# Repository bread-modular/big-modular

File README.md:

# Big Modular

A collection of Eurorack modules built with shared KiCad tooling.

## Modules

| Module | Description | Release |
| --- | --- | --- |
| [`usb-power`](modules/usb-power/) | USB-C PD input → protected 9V, dual TPS54302 bucks, TPS65131 raw ±13.5V, TPS7A4700/TPS7A3301 quiet ±12V, +5V | LDO-R1 source; recovered exports STALE |

Each module is self-contained under `modules/<name>/`:

```text
modules/usb-power/
  hardware/     KiCad project (usb-power.kicad_{pro,sch,pcb}, panel, local libs)
  docs/         design, fabrication and evidence notes
  tools/        module generators/checkers
  tests/        module regression tests
  jlcpcb/       recovered Gerber/BOM/CPL snapshot (STALE until re-export)
```

## Common tooling

`opt/` holds shared, module-independent tooling and must not be copied into modules:

- `opt/kicad-tools/` — native KiCad checks, PCB/schematic edits, JLCPCB export/assembly
- `opt/kicad-routing/` — optional router facade

Read `opt/kicad-tools/skills/kicad-workflow/SKILL.md` and
`opt/kicad-tools/skills/jlcpcb-assembly/SKILL.md` before KiCad or sourcing work.

## Quick check

```sh
python3 -B opt/kicad-tools/kicad_tools.py doctor --config modules/usb-power/tools/kicad-project.json
python3 -B -m unittest discover -s modules/usb-power/tests -v
```

Recovery evidence and remaining release gates: [`modules/usb-power/docs/migration-recovery.md`](modules/usb-power/docs/migration-recovery.md).

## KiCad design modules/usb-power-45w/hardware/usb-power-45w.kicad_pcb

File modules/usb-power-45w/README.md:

# usb-power-45w

USB-C PD Eurorack supply, ±12 V only, on one 4-layer carrier behind a 4HP panel.

> **JLCPCB export S9.5 / R4 (2026-11-26) in [`jlcpcb/`](jlcpcb/README.md):** 148 top parts / 59 rows, no D10, the R4
> U2 thermal vias, smallest hole 0.3 mm. Three pre-order parts were swapped for in-stock ones (fields only: R93/R99
> C860071, U10/U11 C702161 TPS3808G01DBVT, U15 C151394 Diodes 74LVC1G17W5-7). Not supplier-accepted, not built.
>
> **S9.5 / R4 (2026-11-26): U2 thermal copper** (24 vias, bigger B.Cu GND pour; [R4 record](docs/routing/README.md)).
>
> **S9.5 / R3 (2026-11-26): D10 removed after the first-board load test.** The SS1060 input reverse blocker ran hot
> (2.25 W at 3 A on very little copper). U5 IN now sits on VPD and one F.Cu VPD pour runs from F1 to U5
> ([design](docs/design.md#s95--r3-d10-removed-2026-11-26)). Backfeed into the USB source is no longer blocked: never
> parallel another running supply on the ±12 V bus. On a built board, bridge the D10 pads (anode to cathode) to do the
> same.
>
> **S9.4 / R2 (2026-11-16): schematic and routed board fixed after the first-board bench.** The first board
> (S9.3-10P / R1) stayed at 5 V: Q2 in the CH224A supply limiter had emitter and base swapped (SOT89 numbering). S9.4
> removes the limiter; U1 sits straight on VPD ([design](docs/design.md#s94--r2-ch224a-straight-on-vpd-2026-11-16)).
> The S9.4 / R2 export (2026-11-16, 149 top parts / 60 rows) is replaced by the S9.5 / R4 set (git history).
> Not a supplier-accepted release and not bench-qualified. The copper/thermal screen (`tools/check_s8_board.py`) still
> lists contract items; each was reviewed and accepted for the first prototype ([fab review](docs/routing/README.md)).
> **A built R1 board works with a wire from TP1 to TP2** (both on the back), then a re-plug.

## Open

| Open in KiCad | What it is |
| --- | --- |
| **[`hardware/usb-power-45w.kicad_pro`](hardware/usb-power-45w.kicad_pro)** | The module: schematic (`usb-power-45w.kicad_sch` + pages `01`..`05`) and the routed 4-layer PCB (`usb-power-45w.kicad_{pcb,dru}`) |
| [`panels/front-pcb/usb-power-45w-panel.kicad_pro`](panels/front-pcb/usb-power-45w-panel.kicad_pro) | 4HP FR4 front panel (USB-C aperture, MAIN LED, RESET, rail and bracket holes) |
| [`panels/front-cad/`](panels/front-cad/) | 3D-printable 4HP front panel, no labels (STEP/STL/FreeCAD), same holes as the FR4 panel |
| [`panels/bracket/`](panels/bracket/) | The two M3 L brackets (STEP/STL/FreeCAD) |

## Circuit

- **Input:** USB-C PD **15 V / 3 A** (CH224A, R1 56k; VHV/VBUS straight on VPD with 1 µF, the WCH reference circuit).
  U5 TPS16630 main eFuse straight on VPD (S9.5: no D10, no reverse blocking); precision UVLO (on 12.263–12.976 V,
  off 11.365–12.193 V) and OVP (R24 9.1k: 17.30–19.44 V) coordinated with the D24 SMBJ20A clamp.
- **+12 V:** TPS552892-Q1 buck-boost (U2), R109 18 mΩ RLM12 current sense on a 4-terminal Kelvin land.
- **−12 V:** LMR38020 inverting converter (U4) on its own input enable (Q1 on VPD, RUN and MAIN_LED_OK via Q14/Q15),
  sequenced after +12 V (Q16 gate = P12_OK via R118/C86).
- **Strict 3 A start (S9.3):** FB-injection soft starts on both converters (C84/D27/R116 on U2, τ 15 ms nominal;
  C85/D28/R117 on U4, τ 47 ms). Netlist plant: peak input 2.955 A, zero U5 drop-outs in all five cases.
- **Faults:** one-shot `STARTED` arming, always-on latch and RESET button; D8 MAIN is the only panel LED.
- **Output:** two 10-pin shrouded IDC headers J2/J3 (Wurth 61201021621; pins 1/2 −12 V, 3–8 GND, 9/10 +12 V).
  No series reverse blocking (owner decision).
- **Prototype targets:** +12 V 2.4 A / −12 V 0.8 A, ≤ 33 W combined, conditional on the routing contract and the
  post-prototype acceptance tests.

## Status

- Native ERC 0; DRC **0 violations, 0 warnings, 0 exclusions, 0 unconnected**; exact ref/pin/net parity
  (176 refs / 80 nets, S9.5). Manual divide-and-conquer routing, In1 one-piece GND plane, two approved In2 hops.
- Routing contract enforced by native DRC: 8 net classes, 22 `S92_*` rules, 15 rule areas. **No via-in-pad**:
  U4/U5/U9 sit on hole-free lands with thermal-via fields beside the pads (standard 0.3/0.6 mm tented vias).
- All parts on F; test points on B with silkscreen labels. JLCPCB places 149 parts on the top (J1 included;
  the R1 export had 155); J2/J3 (Wurth 61201021621) and D8 (3 mm LED) are hand-fitted.
- **S9.4 / R2 (2026-11-16):** Q2, Q3, R23, R27, D9, D11 and TP2 removed with their copper; U1/C1 re-netted to VPD and
  fed by a 0.4 mm F.Cu link from the VPD via at TP1. No part moved. Record: [docs/routing](docs/routing/README.md).
- **Fab review (2026-11-06):** fixed the two DRC errors left by a KiCad 10 *Update PCB from Schematic* (the SW1
  case-pad link), added a third +12V output via at R109, a third D1 TVS ground via and a U2 PGND via, and moved
  J2/J3/D8 out of the CPL so J1 is machine-placed. D1 SMBJ22A was re-sourced to Littelfuse C224015 (1,947 in stock;
  RUILON C10214 had 59). Export: [`jlcpcb/`](jlcpcb/README.md).
- **Accepted for the first prototype, still listed by `check_s8_board.py`:** minimum widths (taps and short stubs
  only), U2/R109 thermal copper (TH-1 measures it; the D10 item left with D10 in S9.5; R4 added 19 GND + 5 P12_VOUT vias and grew the B.Cu GND pour, so the U2 PGND-via and B.Cu GND items pass, VIN / VOUT F area and R109 +12V remain), U12.14→C52.1 7.63 mm, D25↔D24 9.04 mm, TP22/TP23 pair
  8.25 mm, R116.1 pad edge inside RA_AGND_ISLAND; see the [fab review](docs/routing/README.md). The items in
  [routing-notes.md](docs/design/routing-notes.md) (test points, uncertainty register, routing constraints) are
  post-prototype acceptance tests, not design blockers.

## Read

- [Design and changelog](docs/design.md)
- [Manufacturing export](jlcpcb/README.md) · [Fab review and routing checkpoint](docs/routing/README.md) · [Routing log](docs/routing/continuation-238.md) · [Routing notes](docs/design/routing-notes.md)
- [Schematic PDF](docs/usb-power-45w-schematic.pdf) · [BOM](docs/design/bom.csv) · [Sourcing](docs/design/sourcing.json)
- [Calculations](docs/design/calcs.json) · [Validation](docs/design/validation.json) · [Review record](docs/design/review-s93.json)
- [Assembly PDF](docs/design/assembly/usb-power-45w-placement.pdf) · [STEP](docs/design/assembly/usb-power-45w-assembly.step.zip)
- [Capacitor study](docs/capacitor-study/README.md)

## Rebuild and check

Run from the repository root; raw reports go in the ignored `research/`. The full sequence is in
[docs/design.md](docs/design.md#reproducibility).

```sh
python3 -B modules/usb-power-45w/tools/build_s8.py --output-root <candidate-module-root>
python3 -B opt/kicad-tools/kicad_tools.py check --config modules/usb-power-45w/tools/kicad-project.json --reports <new-dir>
python3 -B -m unittest discover -s modules/usb-power-45w/tools -p 'test_*.py' -v
```

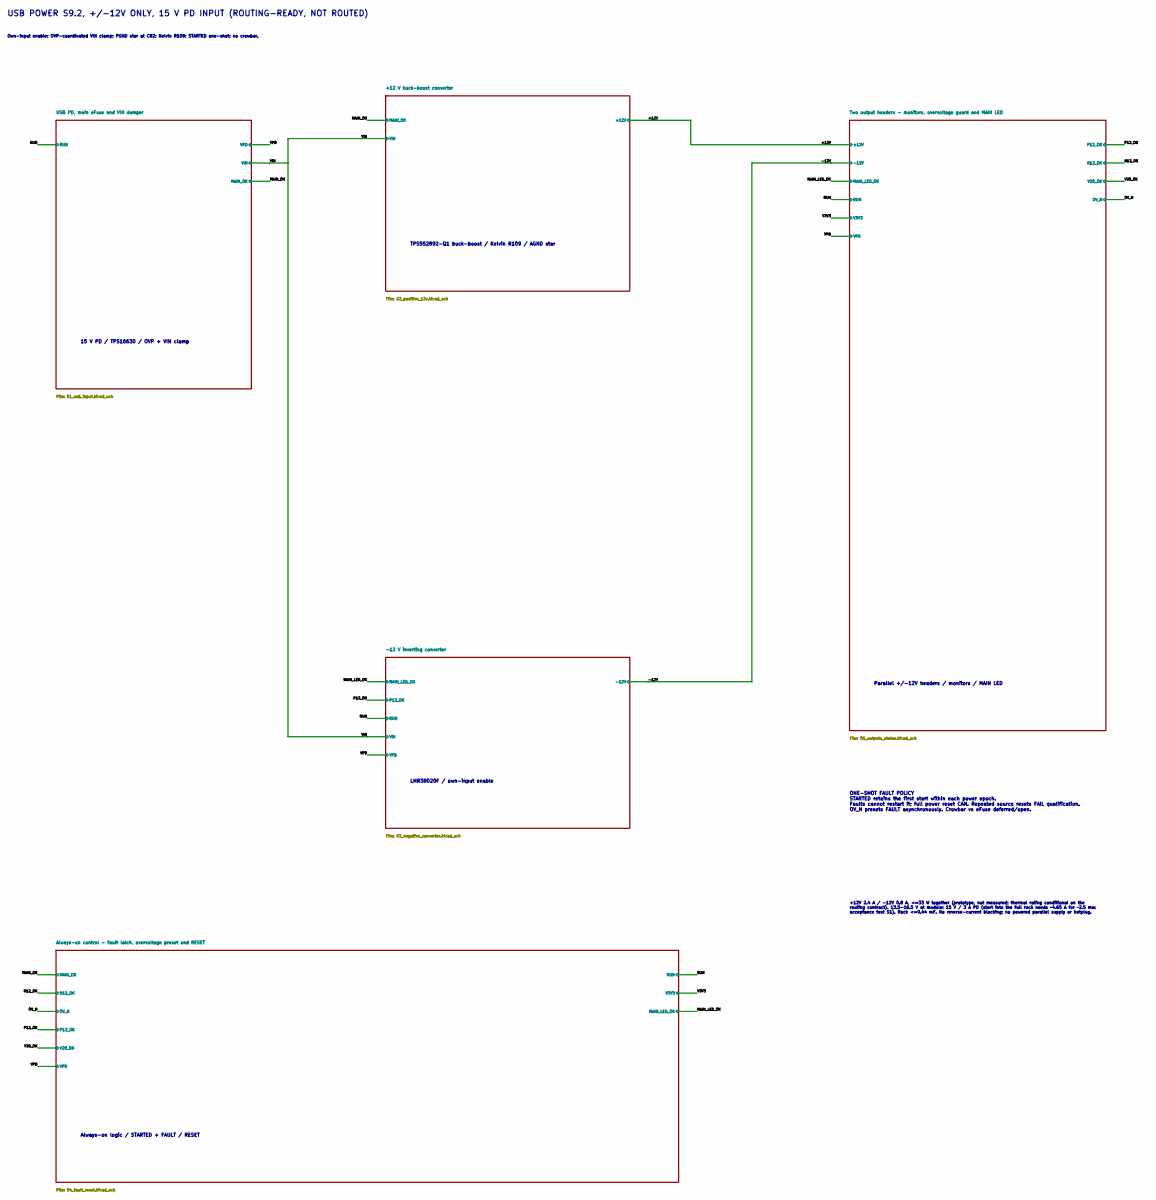
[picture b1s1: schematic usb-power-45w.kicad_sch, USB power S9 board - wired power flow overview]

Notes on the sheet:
ONE-SHOT FAULT POLICY STARTED retains the first start within each power epoch. Faults cannot restart it; full power reset CAN. Repeated source resets FAIL qualification. OV_N presets FAULT asynchronously. Crowbar vs eFuse deferred/open.
TPS552892-Q1 buck-boost / Kelvin R109 / AGND star
USB POWER S9.2, +/-12V ONLY, 15 V PD INPUT (ROUTING-READY, NOT ROUTED)
Parallel +/-12V headers / monitors / MAIN LED
LMR38020F / own-input enable
15 V PD / TPS16630 / OVP + VIN clamp
Own-input enable; OVP-coordinated VIN clamp; PGND star at C82; Kelvin R109; STARTED one-shot; no crowbar.
+12V 2.4 A / -12V 0.8 A, <=33 W together (prototype, not measured; thermal rating conditional on the routing contract). 13.5-16.5 V at module; 15 V / 3 A PD (start into the full rack needs ~4.65 A for ~2.5 ms: acceptance test S1). Rack <=0.44 mF. No reverse-current blocking; no powered parallel sup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
Always-on logic / STARTED + FAULT / RESET

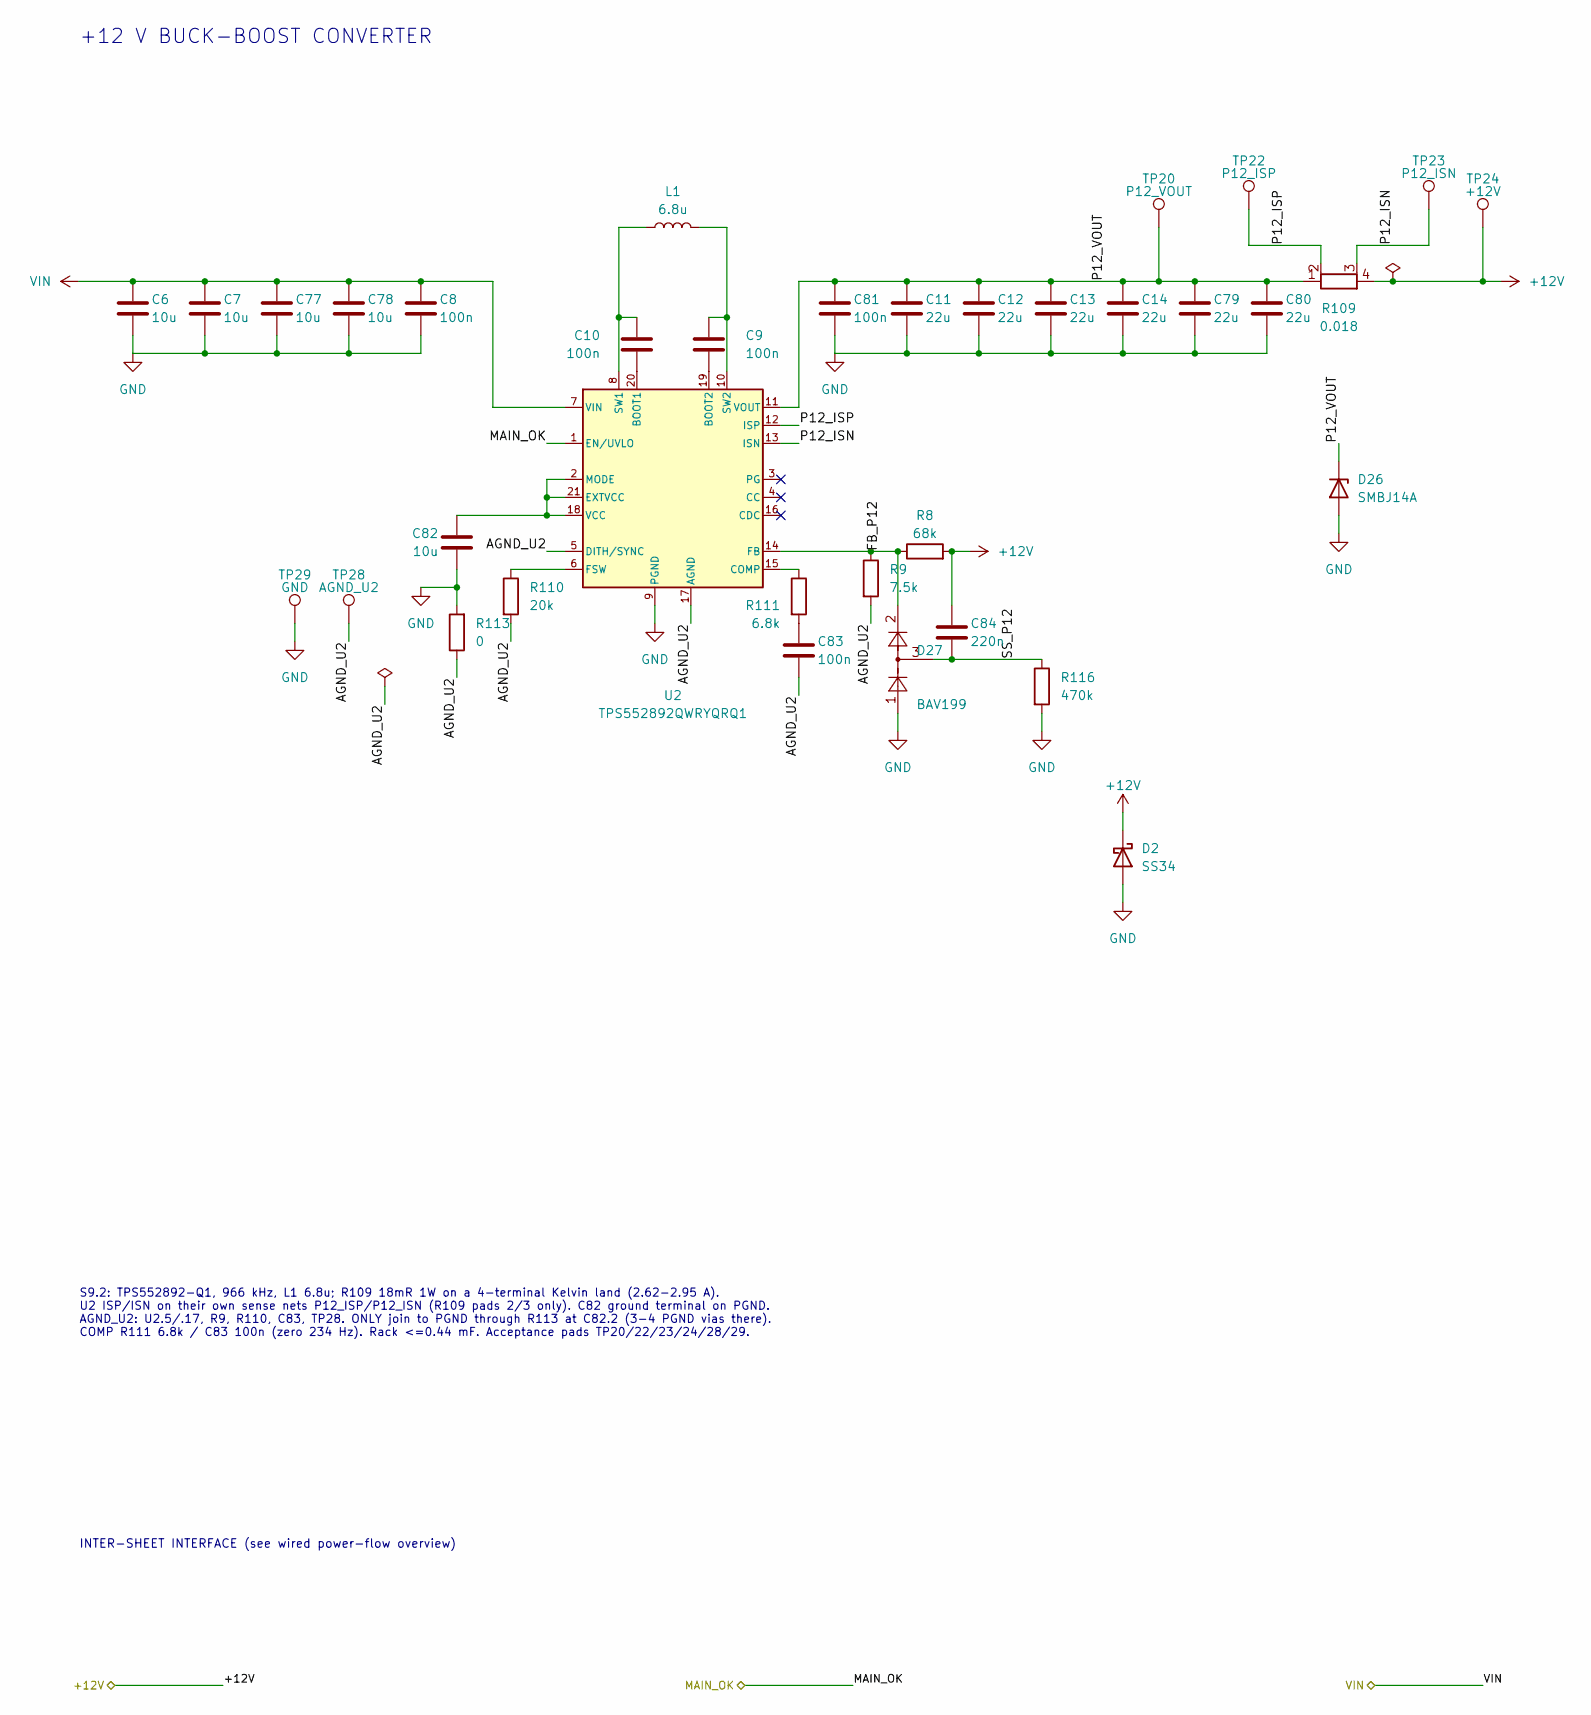
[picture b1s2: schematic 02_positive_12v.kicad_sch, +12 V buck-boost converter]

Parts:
C6, C7, C77, C78, C82: 10u; C_1206_3216Metric; Voltage 50V; MPN CL31A106KBHNNNE; LCSC C13585
C8, C9, C10, C81, C83: 100n; C_0603_1608Metric; Voltage 50V; MPN CC0603KRX7R9BB104; LCSC C14663
C11, C12, C13, C14, C79, C80: 22u; C_1206_3216Metric; Voltage 25V; MPN CL31A226KAHNNNE; LCSC C12891
C84: 220n; C_0603_1608Metric; Voltage 25V; MPN CL10B224KA8NNNC; LCSC C21120
D2: SS34; D_SMA; MPN SS34; LCSC C8678
D26: SMBJ14A; D_SMB; MPN SMBJ14A; LCSC C315990
D27: BAV199; SOT-23; MPN BAV199LT1G; LCSC C145516
L1: 6.8u; L_SLO1040H6R8MTT; MPN SLO1040H6R8MTT; LCSC C207852
R8: 68k; R_0603_1608Metric; Tolerance 1%; MPN 0603WAF6802T5E; LCSC C23231
R9: 7.5k; R_0603_1608Metric; Tolerance 1%; MPN 0603WAF7501T5E; LCSC C23234
R109: 0.018; R_Shunt_1206_KelvinSplit_RLM12; Tolerance 1%; MPN RLM12FTCMR018; LCSC C393095
R110: 20k; R_0603_1608Metric; Tolerance 1%; MPN 0603WAF2002T5E; LCSC C4184
R111: 6.8k; R_0603_1608Metric; Tolerance 1%; MPN 0603WAF6801T5E; LCSC C23212
R113: 0; R_0603_1608Metric; MPN 0603WAF0000T5E; LCSC C21189
R116: 470k; R_0603_1608Metric; Tolerance 1%; MPN 0603WAF4703T5E; LCSC C23178
TP20: P12_VOUT; TestPoint_Pad_D1.5mm
TP22: P12_ISP; TestPoint_Pad_D1.5mm
TP23: P12_ISN; TestPoint_Pad_D1.5mm
TP24: +12V; TestPoint_Pad_D1.5mm
TP28: AGND_U2; TestPoint_Pad_D1.5mm
TP29: GND; TestPoint_Pad_D1.5mm
U2: TPS552892QWRYQRQ1; TI_RYQ0021B_VQFN-HR-21_3x5mm; MPN TPS552892QWRYQRQ1; LCSC C22375748

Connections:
+12V: C84.1, D2.1 (K), R8.2, R109.4, TP24.1 (1_1); also elsewhere on the board
/+12 V buck-boost converter/AGND_U2: C83.2, R9.2, R110.2, R113.1, TP28.1 (1_1), U2.5 (DITH/SYNC), U2.17 (AGND)
/+12 V buck-boost converter/FB_P12: D27.2 (K), R8.1, R9.1, U2.14 (FB)
/+12 V buck-boost converter/P12_ISN: R109.3, TP23.1 (1_1), U2.13 (ISN)
/+12 V buck-boost converter/P12_ISP: R109.2, TP22.1 (1_1), U2.12 (ISP)
/+12 V buck-boost converter/P12_VOUT: C11.1, C12.1, C13.1, C14.1, C79.1, C80.1, C81.1, D26.1 (K), R109.1, TP20.1 (1_1), U2.11 (VOUT)
/+12 V buck-boost converter/SS_P12: C84.2, D27.3 (COM), R116.1
/MAIN_OK: U2.1 (EN/UVLO); also elsewhere on the board
GND: C6.2, C7.2, C8.2, C11.2, C12.2, C13.2, C14.2, C77.2, C78.2, C79.2, C80.2, C81.2, C82.2, D2.2 (A), D26.2 (A), D27.1 (A), R113.2, R116.2, TP29.1 (1_1), U2.9 (PGND); also elsewhere on the board
unnamed: C83.1, R111.2
unnamed: C10.1, U2.20 (BOOT1)
unnamed: C9.1, U2.19 (BOOT2)
unnamed: R111.1, U2.15 (COMP)
unnamed: C82.1, U2.2 (MODE), U2.18 (VCC), U2.21 (EXTVCC)
unnamed: R110.1, U2.6 (FSW)
unnamed: C10.2, L1.1, U2.8 (SW1)
unnamed: C9.2, L1.2, U2.10 (SW2)
VIN: C6.1, C7.1, C8.1, C77.1, C78.1, U2.7 (VIN); also elsewhere on the board

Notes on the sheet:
+12 V BUCK-BOOST CONVERTER
INTER-SHEET INTERFACE (see wired power-flow overview)
S9.2: TPS552892-Q1, 966 kHz, L1 6.8u; R109 18mR 1W on a 4-terminal Kelvin land (2.62-2.95 A). U2 ISP/ISN on their own sense nets P12_ISP/P12_ISN (R109 pads 2/3 only). C82 ground terminal on PGND. AGND_U2: U2.5/.17, R9, R110, C83, TP28. ONLY join to PGND through R113 at C82.2 (3-4 PGND vias there). 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

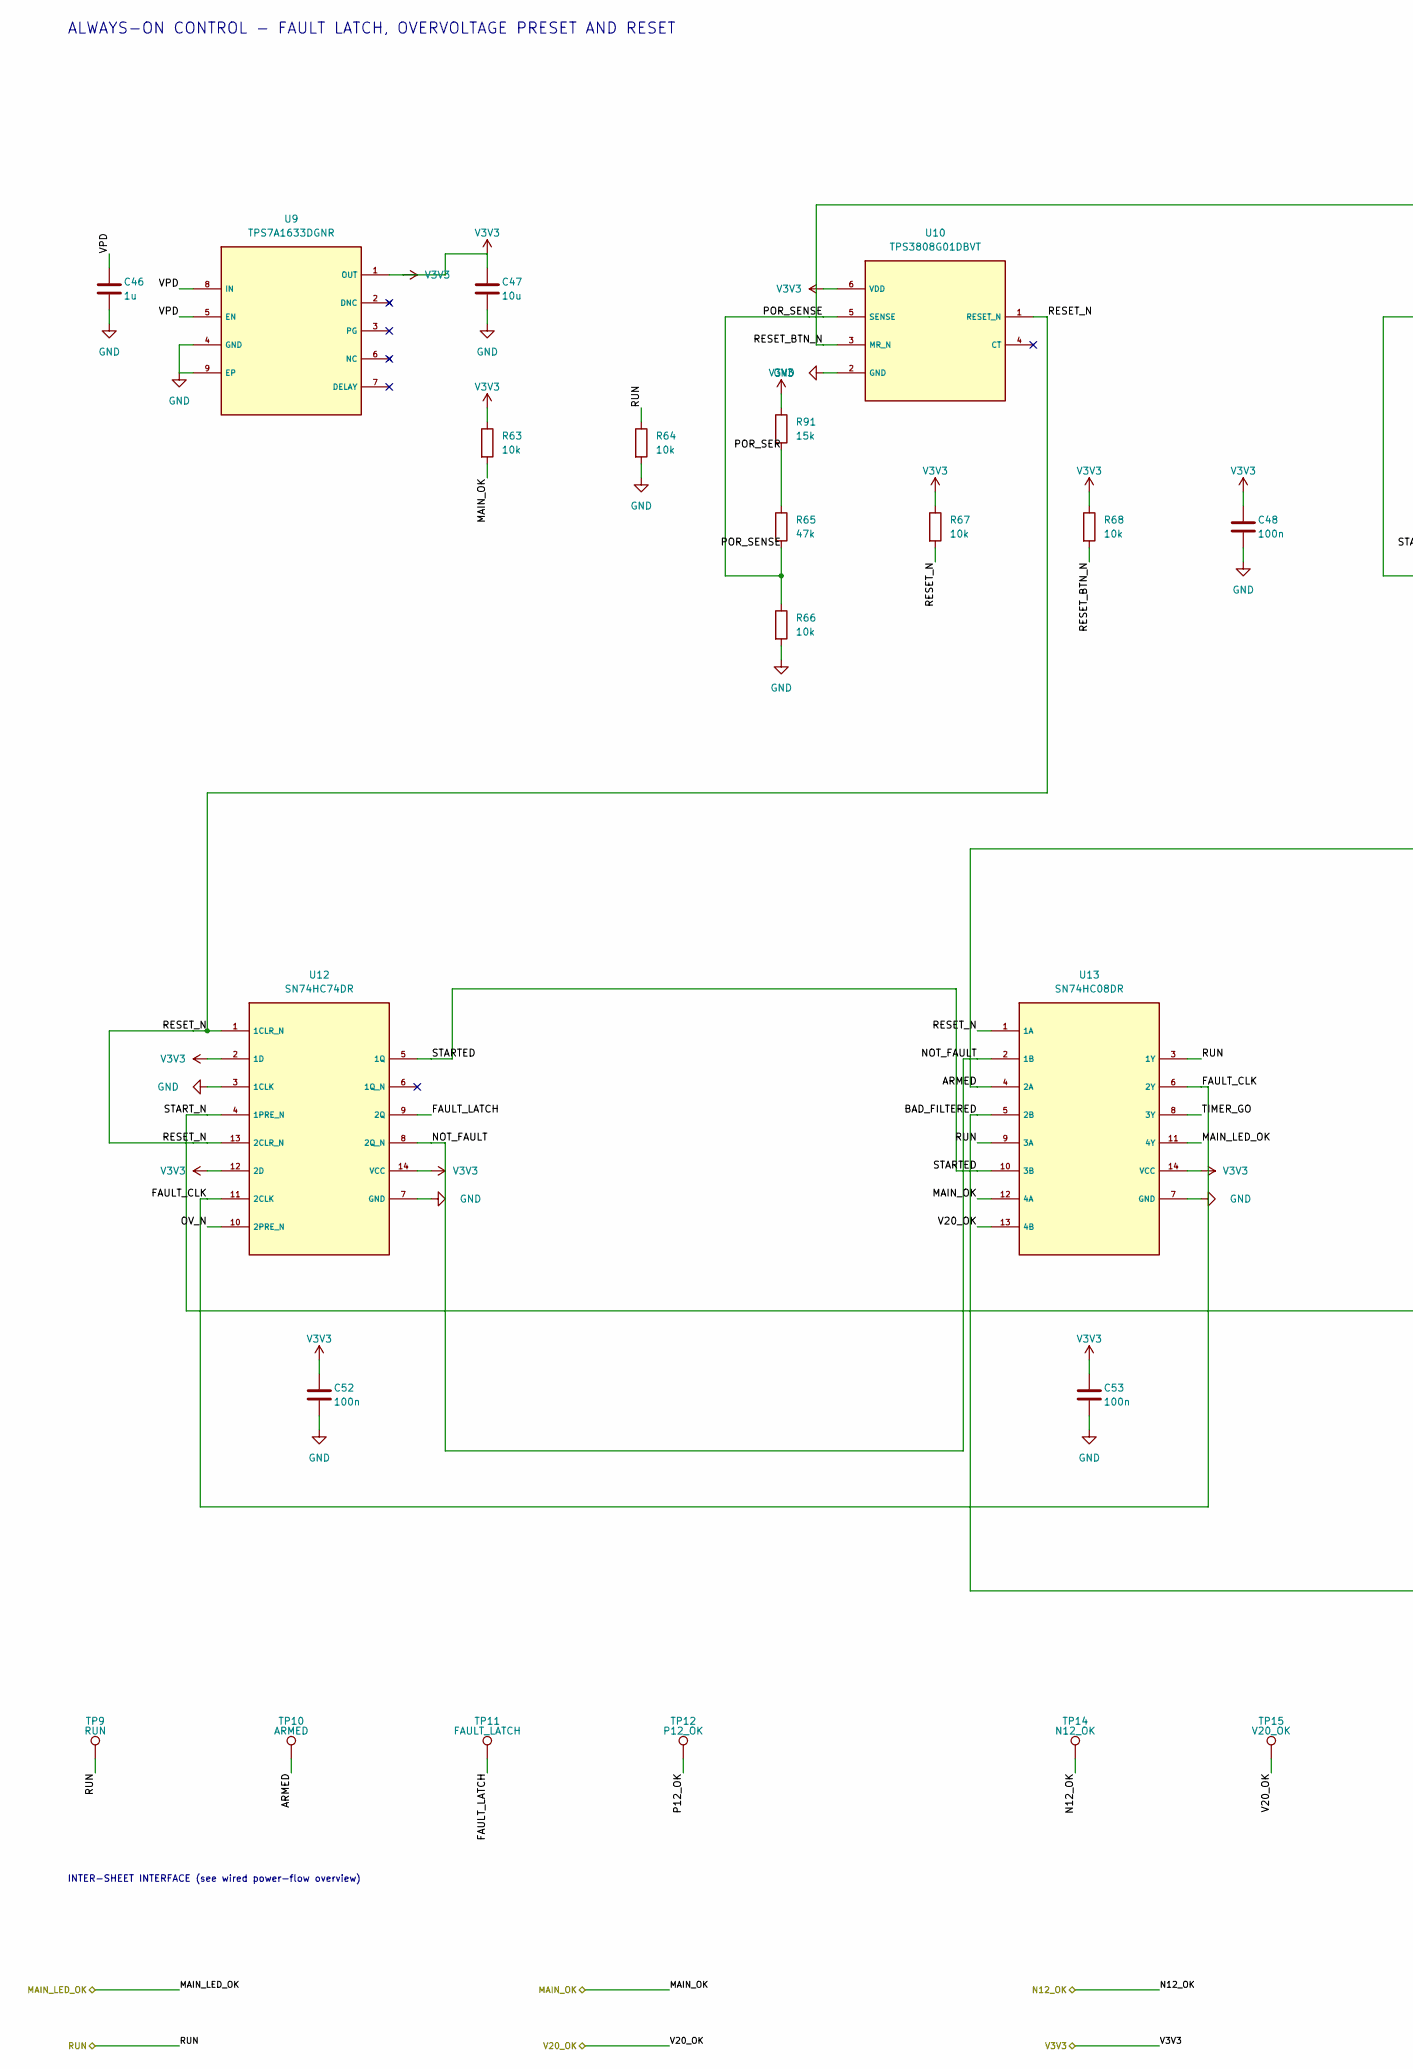
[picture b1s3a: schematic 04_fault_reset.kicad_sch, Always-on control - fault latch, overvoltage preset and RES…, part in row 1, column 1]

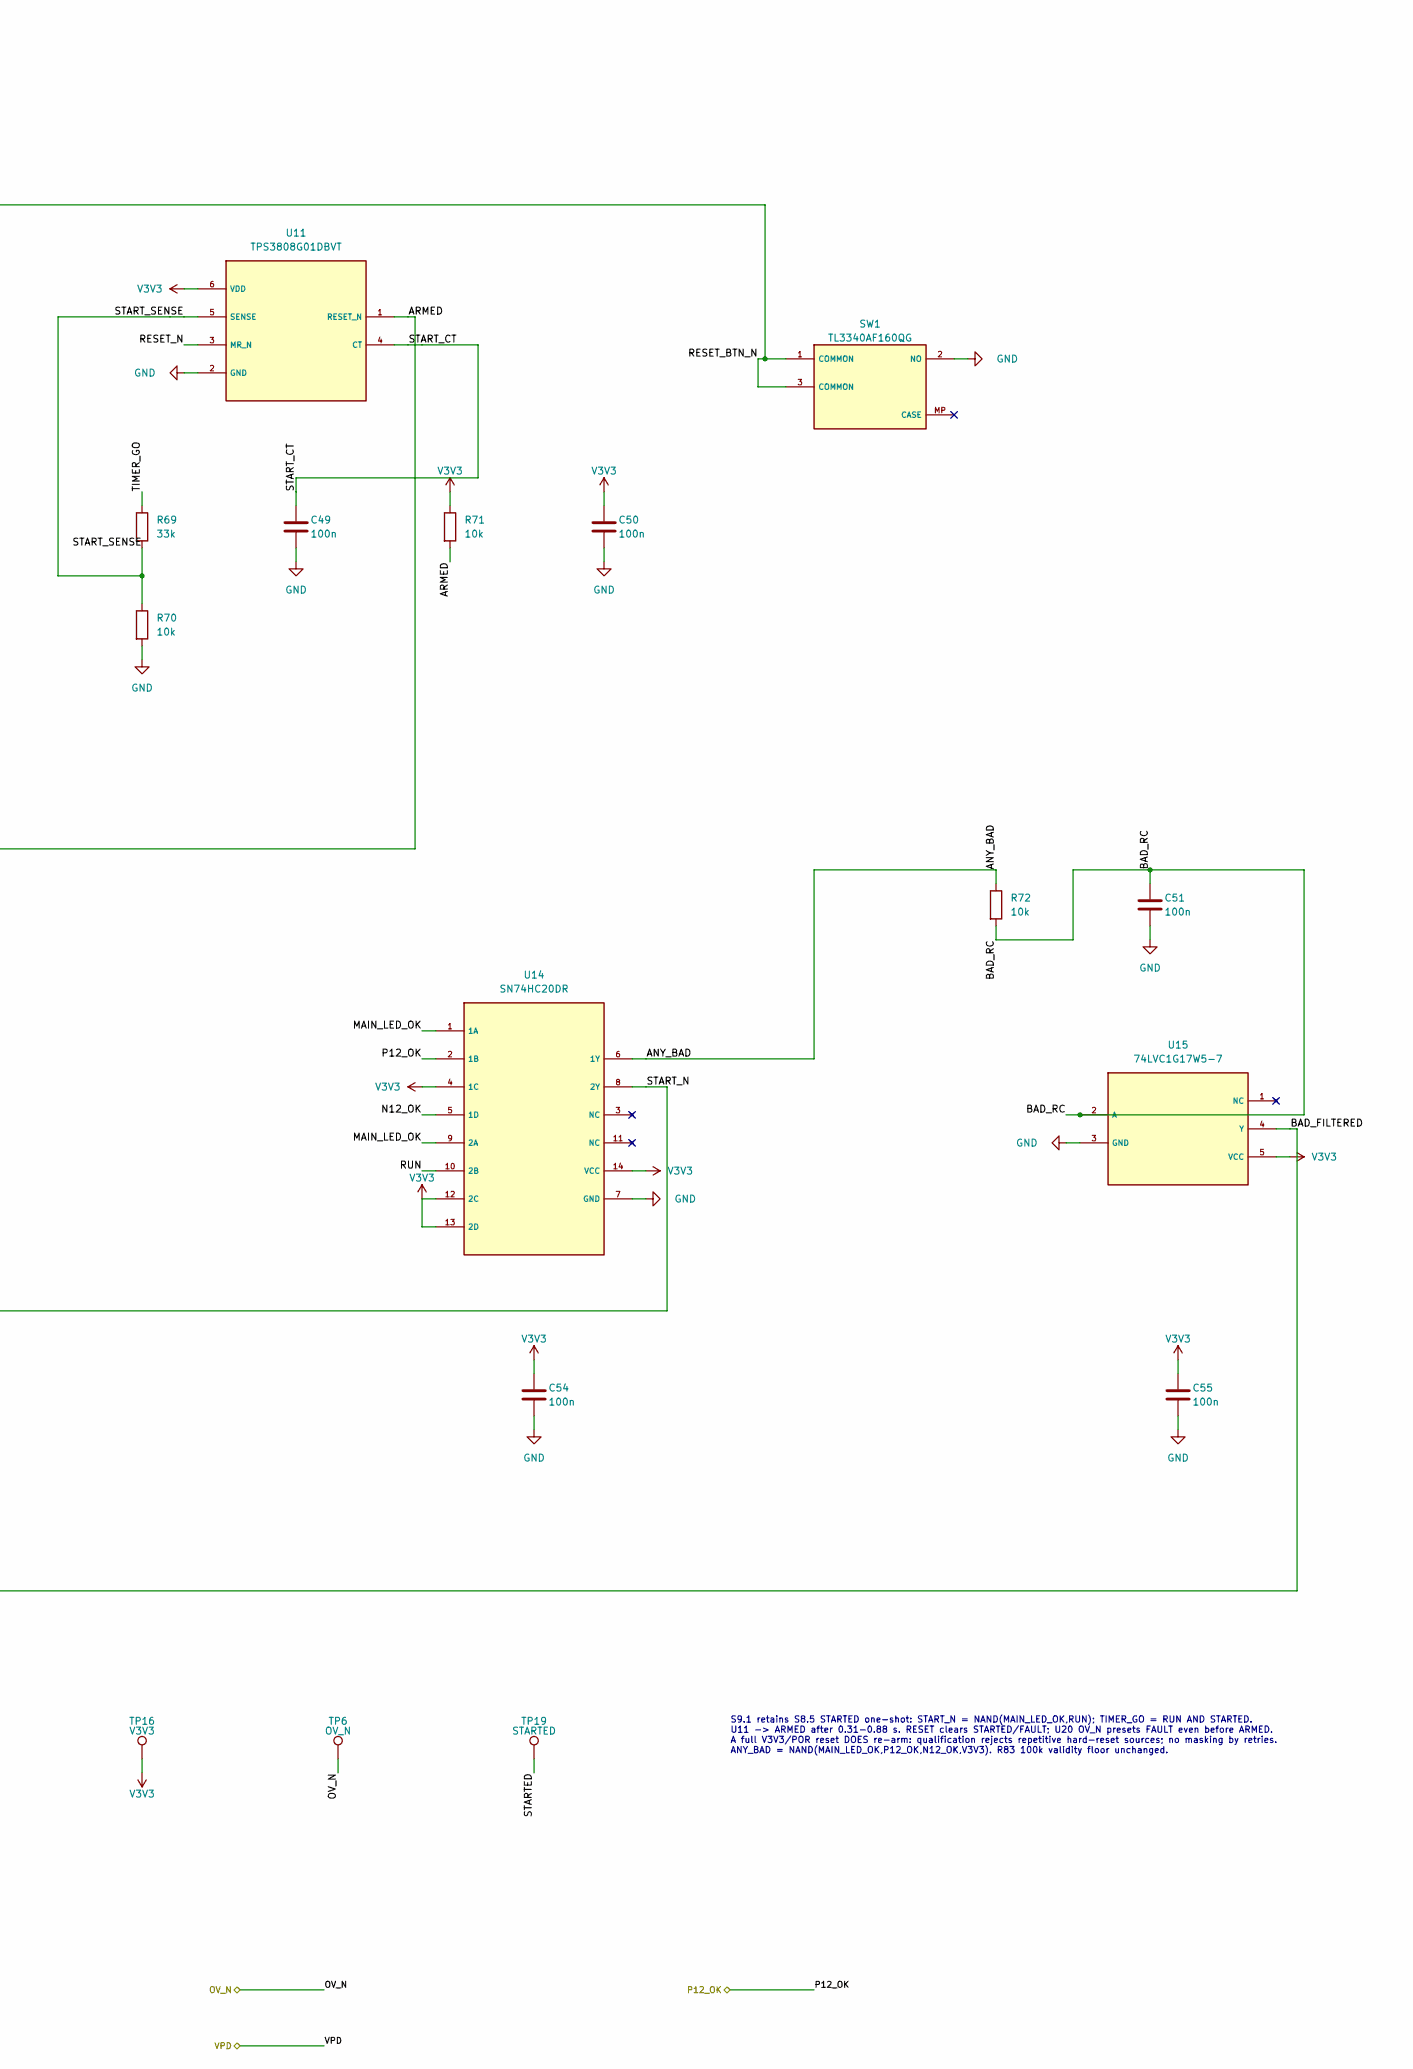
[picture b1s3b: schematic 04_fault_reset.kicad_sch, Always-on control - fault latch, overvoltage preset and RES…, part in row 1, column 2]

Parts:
C46: 1u; C_0603_1608Metric; Voltage 50V; MPN CL10A105KB8NNNC; LCSC C15849
C47: 10u; C_1206_3216Metric; Voltage 50V; MPN CL31A106KBHNNNE; LCSC C13585
C48, C49, C50, C51, C52, C53, C54, C55: 100n; C_0603_1608Metric; Voltage 50V; MPN CC0603KRX7R9BB104; LCSC C14663
R63, R64, R66, R67, R68, R70, R71, R72: 10k; R_0603_1608Metric; Tolerance 1%; MPN 0603WAF1002T5E; LCSC C25804
R65: 47k; R_0603_1608Metric; Tolerance 1%; MPN 0603WAF4702T5E; LCSC C25819
R69: 33k; R_0603_1608Metric; Tolerance 1%; MPN 0603WAF3302T5E; LCSC C4216
R91: 15k; R_0603_1608Metric; Tolerance 1%; MPN 0603WAF1502T5E; LCSC C22809
SW1: TL3340AF160QG; SW_TL3340AF160QG_HandSolder; MPN TL3340AF160QG; LCSC C2886925
TP6: OV_N; TestPoint_Pad_D1.0mm
TP9: RUN; TestPoint_Pad_D1.0mm
TP10: ARMED; TestPoint_Pad_D1.0mm
TP11: FAULT_LATCH; TestPoint_Pad_D1.0mm
TP12: P12_OK; TestPoint_Pad_D1.0mm
TP14: N12_OK; TestPoint_Pad_D1.0mm
TP15: V20_OK; TestPoint_Pad_D1.0mm
TP16: V3V3; TestPoint_Pad_D1.0mm
TP19: STARTED; TestPoint_Pad_D1.0mm
U9: TPS7A1633DGNR; TPS7A16_DGN0008C_NoViaInPad; MPN TPS7A1633DGNR; LCSC C181239
U10, U11: TPS3808G01DBVT; SOT-23-6; MPN TPS3808G01DBVT; LCSC C702161
U12: SN74HC74DR; SOIC-14_3.9x8.7mm_P1.27mm; MPN SN74HC74DR; LCSC C6762
U13: SN74HC08DR; SOIC-14_3.9x8.7mm_P1.27mm; MPN SN74HC08DR; LCSC C337768
U14: SN74HC20DR; SOIC-14_3.9x8.7mm_P1.27mm; MPN SN74HC20DR; LCSC C2867684
U15: 74LVC1G17W5-7; SOT-23-5; MPN 74LVC1G17W5-7; LCSC C151394

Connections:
/Always-on control - fault latch, overvoltage preset and RESET/ANY_BAD: R72.1, U14.6 (1Y)
/Always-on control - fault latch, overvoltage preset and RESET/ARMED: R71.2, TP10.1 (1_1), U11.1 (RESET_N), U13.4 (2A)
/Always-on control - fault latch, overvoltage preset and RESET/BAD_FILTERED: U13.5 (2B), U15.4 (Y)
/Always-on control - fault latch, overvoltage preset and RESET/BAD_RC: C51.1, R72.2, U15.2 (A)
/Always-on control - fault latch, overvoltage preset and RESET/FAULT_CLK: U12.11 (2CLK), U13.6 (2Y)
/Always-on control - fault latch, overvoltage preset and RESET/FAULT_LATCH: TP11.1 (1_1), U12.9 (2Q)
/Always-on control - fault latch, overvoltage preset and RESET/NOT_FAULT: U12.8 (2Q_N), U13.2 (1B)
/Always-on control - fault latch, overvoltage preset and RESET/POR_SENSE: R65.2, R66.1, U10.5 (SENSE)
/Always-on control - fault latch, overvoltage preset and RESET/POR_SER: R65.1, R91.2
/Always-on control - fault latch, overvoltage preset and RESET/RESET_BTN_N: R68.2, SW1.1 (COMMON), SW1.3 (COMMON), U10.3 (MR_N)
/Always-on control - fault latch, overvoltage preset and RESET/RESET_N: R67.2, U10.1 (RESET_N), U11.3 (MR_N), U12.1 (1CLR_N), U12.13 (2CLR_N), U13.1 (1A)
/Always-on control - fault latch, overvoltage preset and RESET/STARTED: TP19.1 (1_1), U12.5 (1Q), U13.10 (3B)
/Always-on control - fault latch, overvoltage preset and RESET/START_CT: C49.1, U11.4 (CT)
/Always-on control - fault latch, overvoltage preset and RESET/START_N: U12.4 (1PRE_N), U14.8 (2Y)
/Always-on control - fault latch, overvoltage preset and RESET/START_SENSE: R69.2, R70.1, U11.5 (SENSE)
/Always-on control - fault latch, overvoltage preset and RESET/TIMER_GO: R69.1, U13.8 (3Y)
/MAIN_LED_OK: U13.11 (4Y), U14.1 (1A), U14.9 (2A); also elsewhere on the board
/MAIN_OK: R63.2, U13.12 (4A); also elsewhere on the board
/N12_OK: TP14.1 (1_1), U14.5 (1D); also elsewhere on the board
/OV_N: TP6.1 (1_1), U12.10 (2PRE_N); also elsewhere on the board
/P12_OK: TP12.1 (1_1), U14.2 (1B); also elsewhere on the board
/RUN: R64.1, TP9.1 (1_1), U13.3 (1Y), U13.9 (3A), U14.10 (2B); also elsewhere on the board
/V20_OK: TP15.1 (1_1), U13.13 (4B); also elsewhere on the board
/VPD: C46.1, U9.5 (EN), U9.8 (IN); also elsewhere on the board
GND: C46.2, C47.2, C48.2, C49.2, C50.2, C51.2, C52.2, C53.2, C54.2, C55.2, R64.2, R66.2, R70.2, SW1.2 (NO), U9.4 (GND), U9.9 (EP), U10.2 (GND), U11.2 (GND), U12.3 (1CLK), U12.7 (GND), U13.7 (GND), U14.7 (GND), U15.3 (GND); also elsewhere on the board
V3V3: C47.1, C48.1, C50.1, C52.1, C53.1, C54.1, C55.1, R63.1, R67.1, R68.1, R71.1, R91.1, TP16.1 (1_1), U9.1 (OUT), U10.6 (VDD), U11.6 (VDD), U12.2 (1D), U12.12 (2D), U12.14 (VCC), U13.14 (VCC), U14.4 (1C), U14.12 (2C), U14.13 (2D), U14.14 (VCC), U15.5 (VCC); also elsewhere on the board

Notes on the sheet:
ALWAYS-ON CONTROL - FAULT LATCH, OVERVOLTAGE PRESET AND RESET
INTER-SHEET INTERFACE (see wired power-flow overview)
S9.1 retains S8.5 STARTED one-shot: START_N = NAND(MAIN_LED_OK,RUN); TIMER_GO = RUN AND STARTED. U11 -> ARMED after 0.31-0.88 s. RESET clears STARTED/FAULT; U20 OV_N presets FAULT even before ARMED. A full V3V3/POR reset DOES re-arm: qualification rejects repetitive hard-reset sources; no masking b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

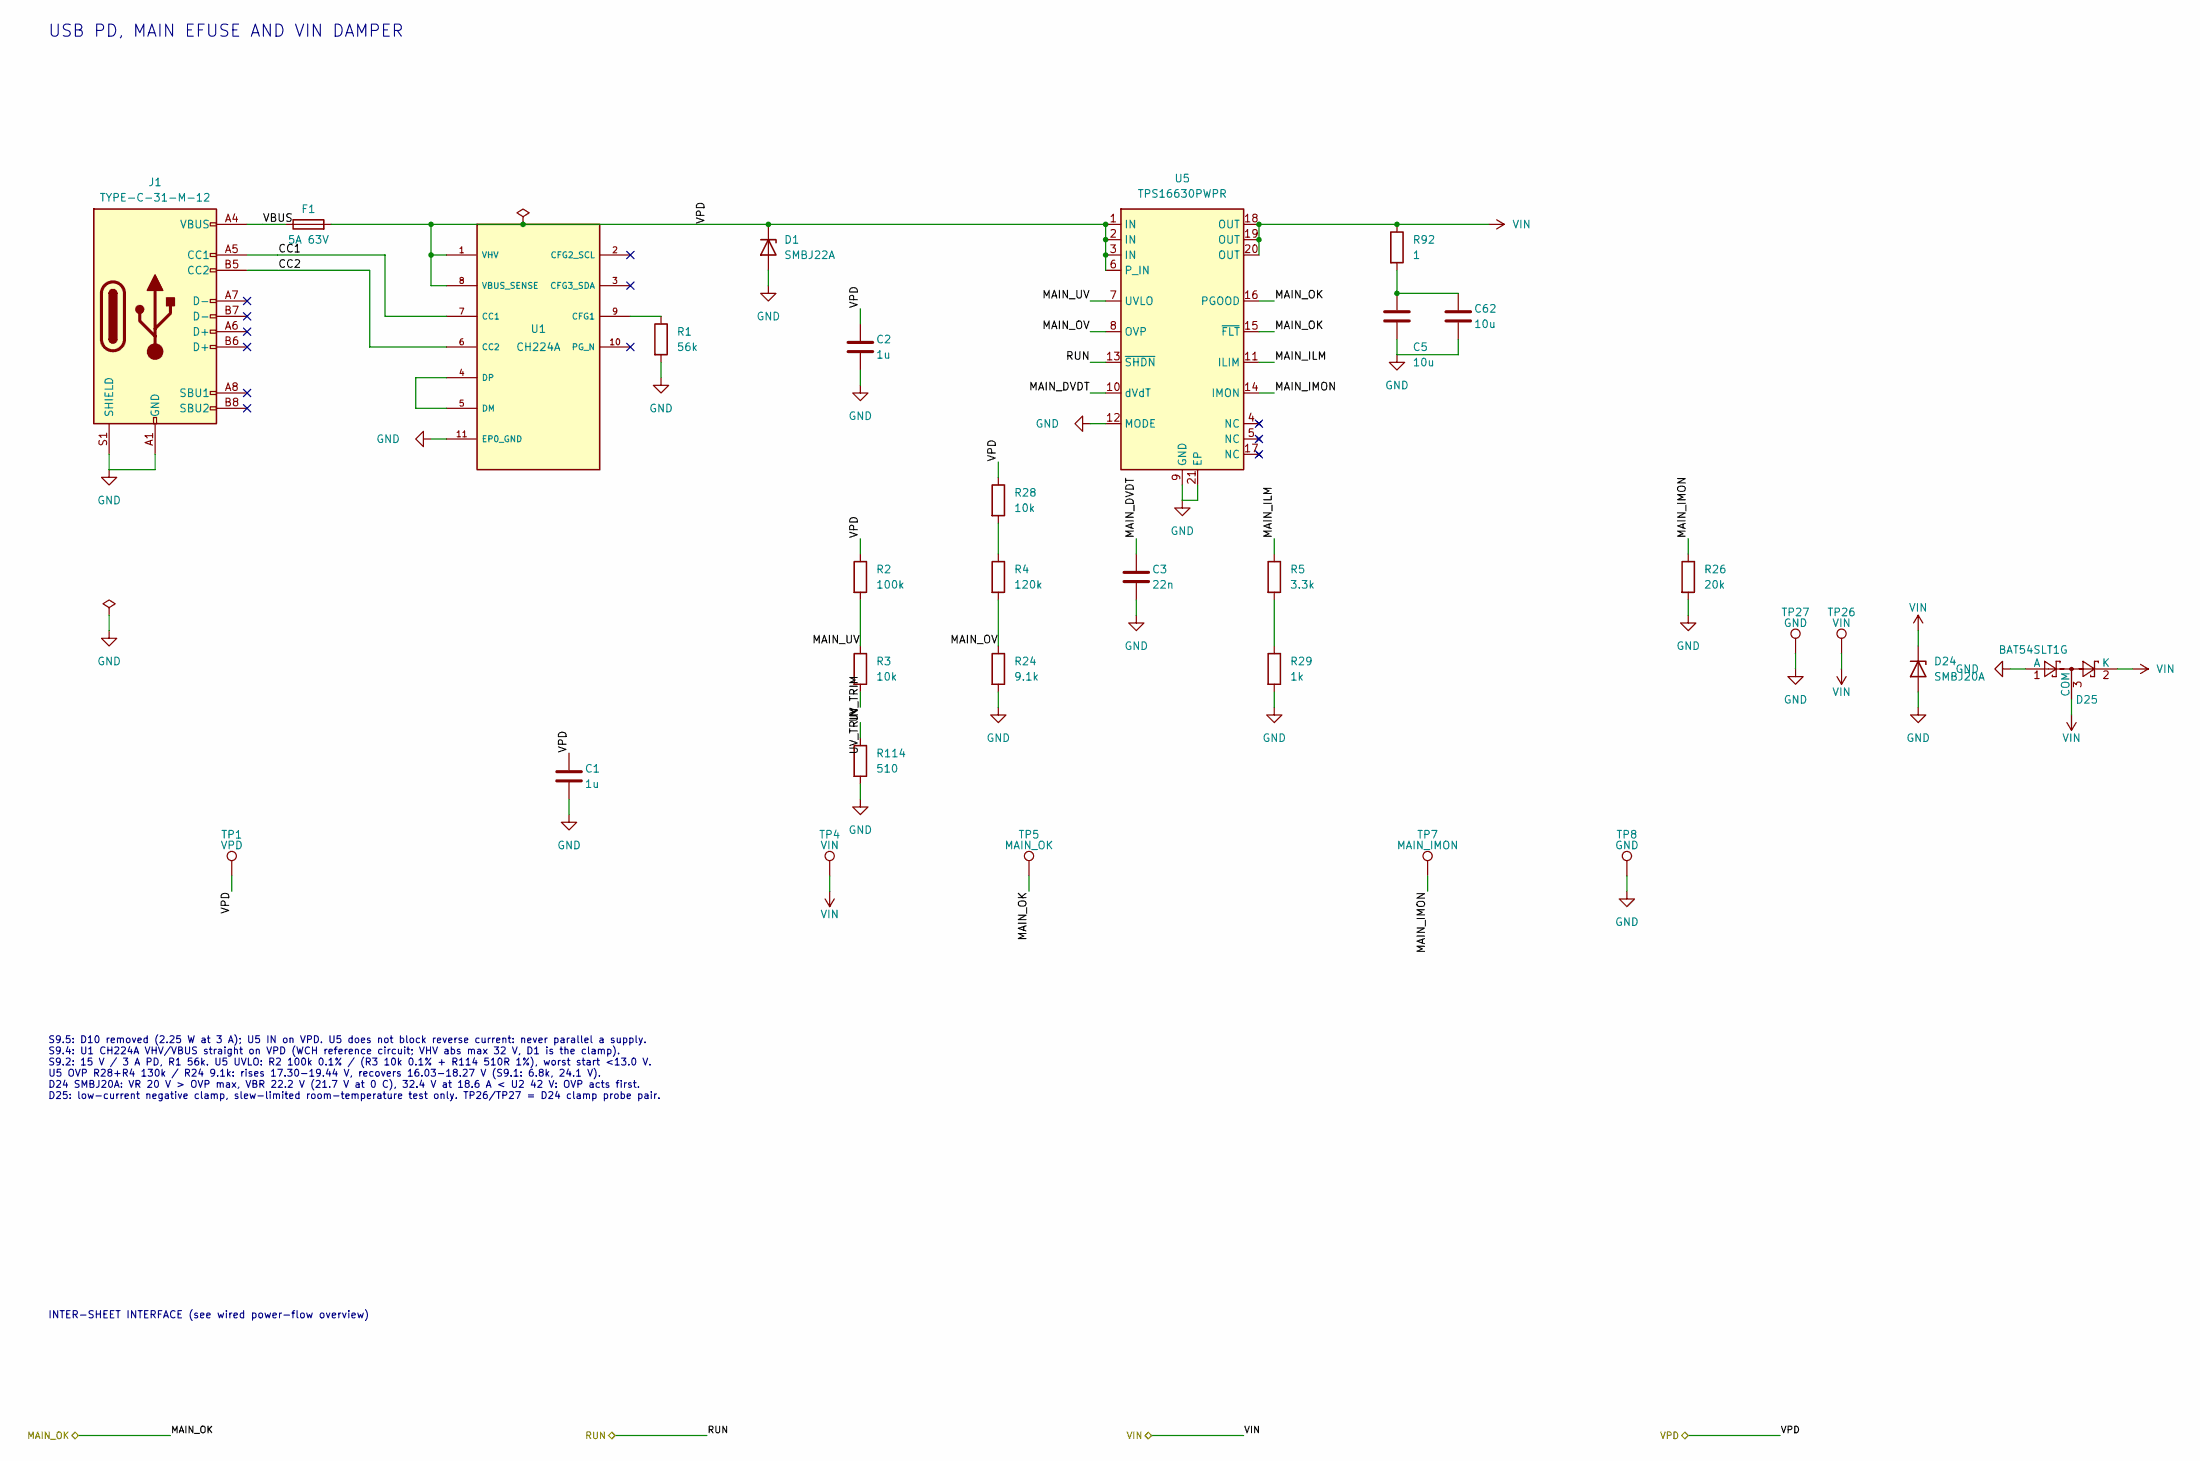
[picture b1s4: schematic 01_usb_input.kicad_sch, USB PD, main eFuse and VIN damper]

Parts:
C1, C2: 1u; C_0603_1608Metric; Voltage 50V; MPN CL10A105KB8NNNC; LCSC C15849
C3: 22n; C_0603_1608Metric; Voltage 50V; MPN CL10B223KB8NNNC; LCSC C21122
C5, C62: 10u; C_1206_3216Metric; Voltage 50V; MPN CL31A106KBHNNNE; LCSC C13585
D1: SMBJ22A; D_SMB; MPN SMBJ22A; LCSC C224015
D24: SMBJ20A; D_SMB; MPN SMBJ20A; LCSC C151257
D25: BAT54SLT1G; SOT-23; MPN BAT54SLT1G; LCSC C19726
F1: 5A 63V; Fuse_1206_3216Metric; MPN S1206-SD-5.0A; LCSC C553937
J1: TYPE-C-31-M-12; HRO-TYPE-C-31-M-12; MPN TYPE-C-31-M-12; LCSC C165948
R1: 56k; R_0603_1608Metric; Tolerance 1%; MPN 0603WAF5602T5E; LCSC C23206
R2: 100k; R_0603_1608Metric; Tolerance 0.1%; MPN RT0603BRD07100KL; LCSC C122538
R3: 10k; R_0603_1608Metric; Tolerance 0.1%; MPN RT0603BRD0710KL; LCSC C95204
R4: 120k; R_0603_1608Metric; Tolerance 1%; MPN 0603WAF1203T5E; LCSC C25808
R5: 3.3k; R_0603_1608Metric; Tolerance 1%; MPN 0603WAF3301T5E; LCSC C22978
R24: 9.1k; R_0603_1608Metric; Tolerance 1%; MPN 0603WAF9101T5E; LCSC C23260
R26: 20k; R_0603_1608Metric; Tolerance 1%; MPN 0603WAF2002T5E; LCSC C4184
R28: 10k; R_0603_1608Metric; Tolerance 1%; MPN 0603WAF1002T5E; LCSC C25804
R29: 1k; R_0603_1608Metric; Tolerance 1%; MPN 0603WAF1001T5E; LCSC C21190
R92: 1; R_1206_3216Metric; Tolerance 1%; MPN 1206W4F100KT5E; LCSC C17928
R114: 510; R_0603_1608Metric; Tolerance 1%; MPN 0603WAF5100T5E; LCSC C23193
TP1: VPD; TestPoint_Pad_D1.0mm
TP4: VIN; TestPoint_Pad_D1.0mm
TP5: MAIN_OK; TestPoint_Pad_D1.0mm
TP7: MAIN_IMON; TestPoint_Pad_D1.0mm
TP8: GND; TestPoint_Pad_D1.0mm
TP26: VIN; TestPoint_Pad_D1.5mm
TP27: GND; TestPoint_Pad_D1.5mm
U1: CH224A; SSOP-10-1EP_3.9x4.9mm_P1mm_EP2.1x3.3mm; MPN CH224A; LCSC C42459160
U5: TPS16630PWPR; HTSSOP-20-1EP_4.4x6.5mm_P0.65mm_EP3.4x6.5mm_Mask2.96x2.96mm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; MPN TPS16630PWPR; LCSC C1849461

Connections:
/MAIN_OK: TP5.1 (1_1), U5.15 (~FLT), U5.16 (PGOOD); also elsewhere on the board
/RUN: U5.13 (~SHDN); also elsewhere on the board
/USB PD, main eFuse and VIN damper/CC1: J1.A5 (CC1), U1.7 (CC1)
/USB PD, main eFuse and VIN damper/CC2: J1.B5 (CC2), U1.6 (CC2)
/USB PD, main eFuse and VIN damper/MAIN_DVDT: C3.1, U5.10 (dVdT)
/USB PD, main eFuse and VIN damper/MAIN_ILM: R5.1, U5.11 (ILIM)
/USB PD, main eFuse and VIN damper/MAIN_IMON: R26.1, TP7.1 (1_1), U5.14 (IMON)
/USB PD, main eFuse and VIN damper/MAIN_OV: R4.2, R24.1, U5.8 (OVP)
/USB PD, main eFuse and VIN damper/MAIN_UV: R2.2, R3.1, U5.7 (UVLO)
/USB PD, main eFuse and VIN damper/UV_TRIM: R3.2, R114.1
/USB PD, main eFuse and VIN damper/VBUS: F1.1, J1.A4 (VBUS), J1.A9 (VBUS)
/VPD: C1.1, C2.1, D1.1 (K), F1.2, R2.1, R28.1, TP1.1 (1_1), U1.1 (VHV), U1.8 (VBUS_SENSE), U5.1 (IN), U5.2 (IN), U5.3 (IN), U5.6 (P_IN); also elsewhere on the board
GND: C1.2, C2.2, C3.2, C5.2, C62.2, D1.2 (A), D24.2 (A), D25.1 (A), J1.A1 (GND), J1.A12 (GND), J1.S1 (SHIELD), R1.2, R24.2, R26.2, R29.2, R114.2, TP8.1 (1_1), TP27.1 (1_1), U1.11 (EP0_GND), U5.9 (GND), U5.12 (MODE), U5.21 (EP); also elsewhere on the board
unnamed: C5.1, C62.1, R92.2
unnamed: R4.1, R28.2
unnamed: R5.2, R29.1
unnamed: R1.1, U1.9 (CFG1)
unnamed: U1.4 (DP), U1.5 (DM)
VIN: D24.1 (K), D25.2 (K), D25.3 (COM), R92.1, TP4.1 (1_1), TP26.1 (1_1), U5.18 (OUT), U5.19 (OUT), U5.20 (OUT); also elsewhere on the board

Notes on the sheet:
USB PD, MAIN EFUSE AND VIN DAMPER
INTER-SHEET INTERFACE (see wired power-flow overview)
S9.5: D10 removed (2.25 W at 3 A); U5 IN on VPD. U5 does not block reverse current: never parallel a supply. S9.4: U1 CH224A VHV/VBUS straight on VPD (WCH reference circuit; VHV abs max 32 V, D1 is the clamp). S9.2: 15 V / 3 A PD, R1 56k. U5 UVLO: R2 100k 0.1% / (R3 10k 0.1% + R114 510R 1%), worst 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
